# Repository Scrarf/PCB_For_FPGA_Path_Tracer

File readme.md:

# Work in progress!

PCB for [FPGA\_Path\_tracer](https://github.com/Scrarf/FPGA_Path_Tracer).

# Schematic

# Layout (WIP)

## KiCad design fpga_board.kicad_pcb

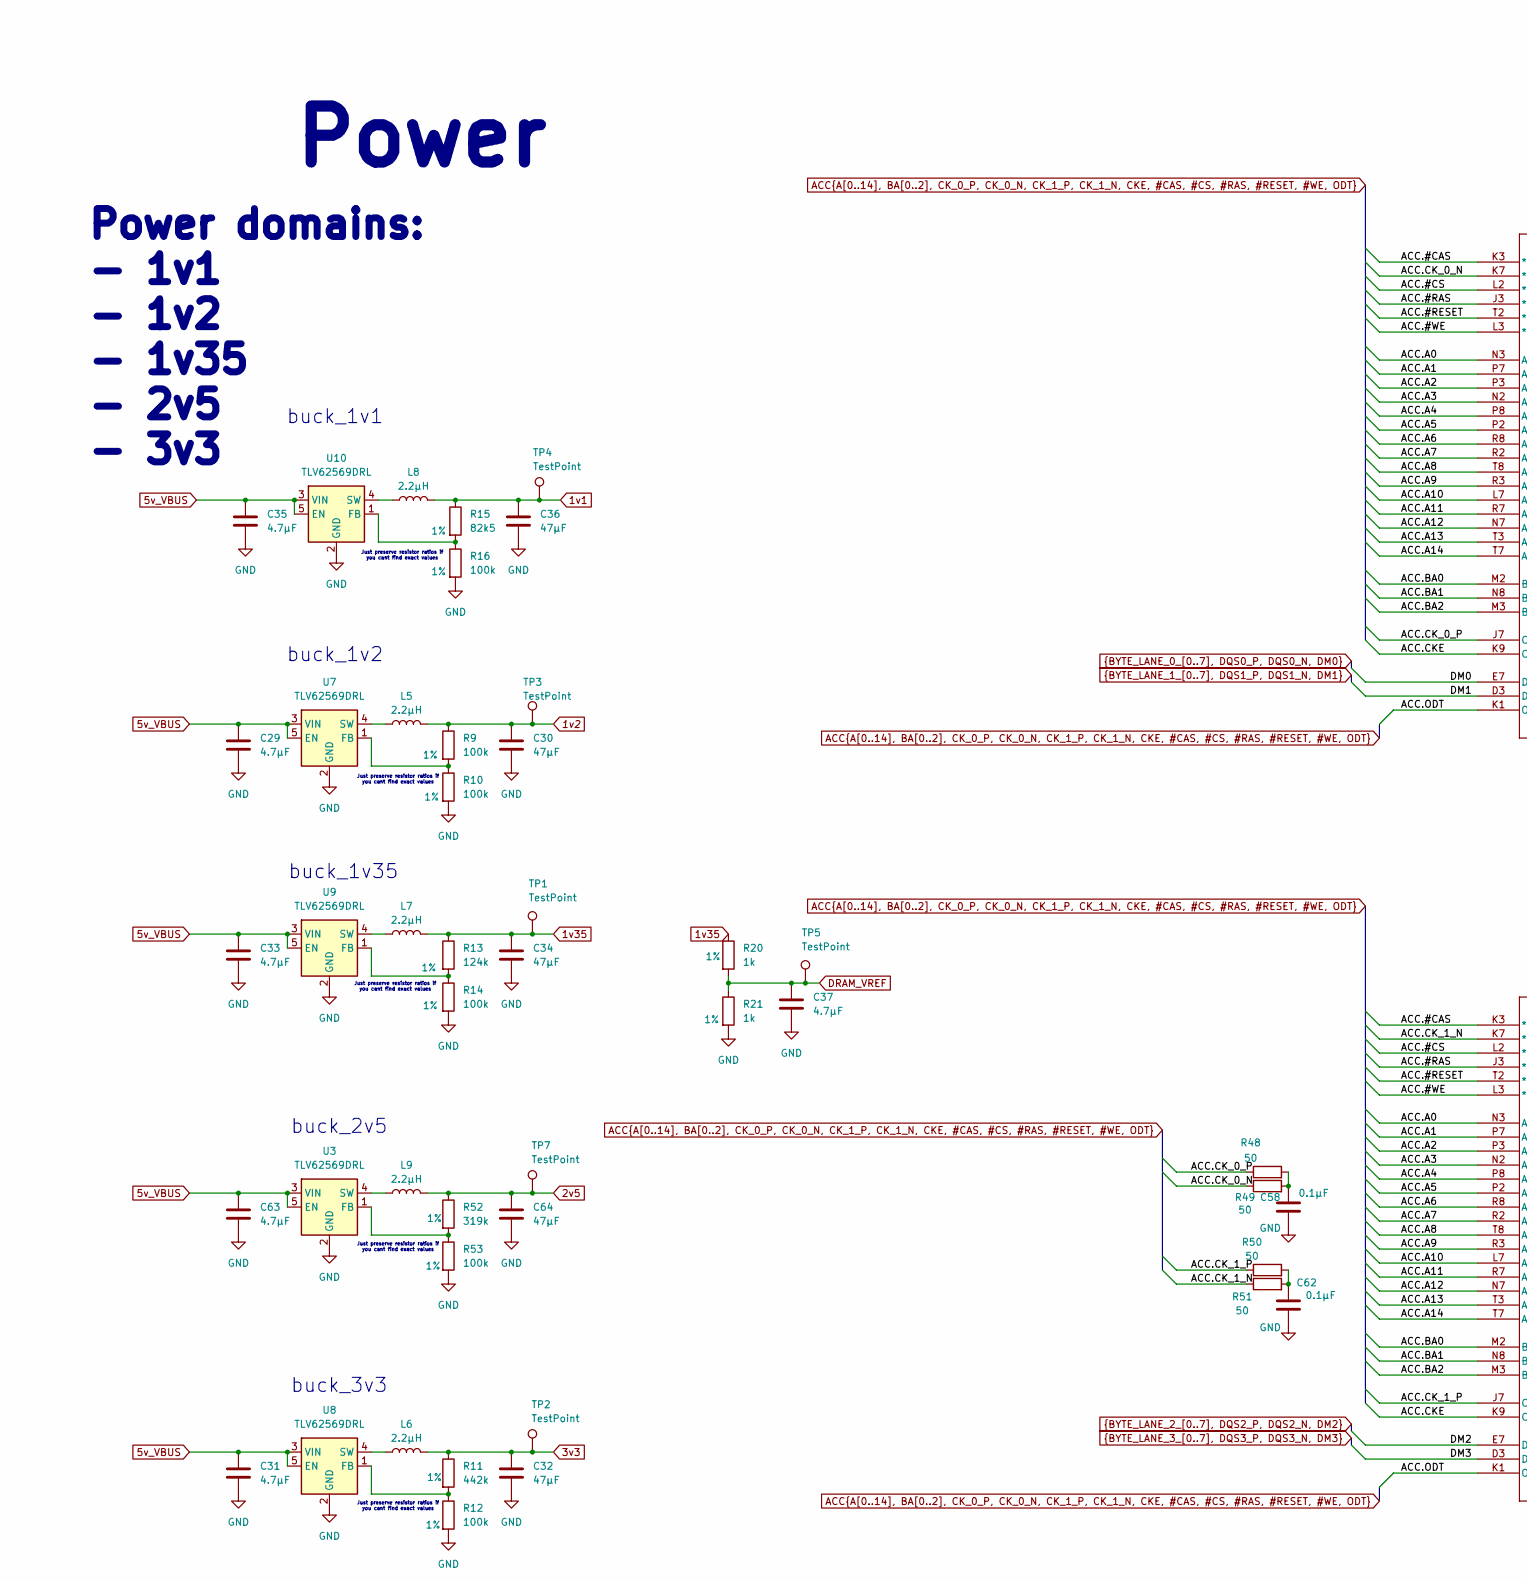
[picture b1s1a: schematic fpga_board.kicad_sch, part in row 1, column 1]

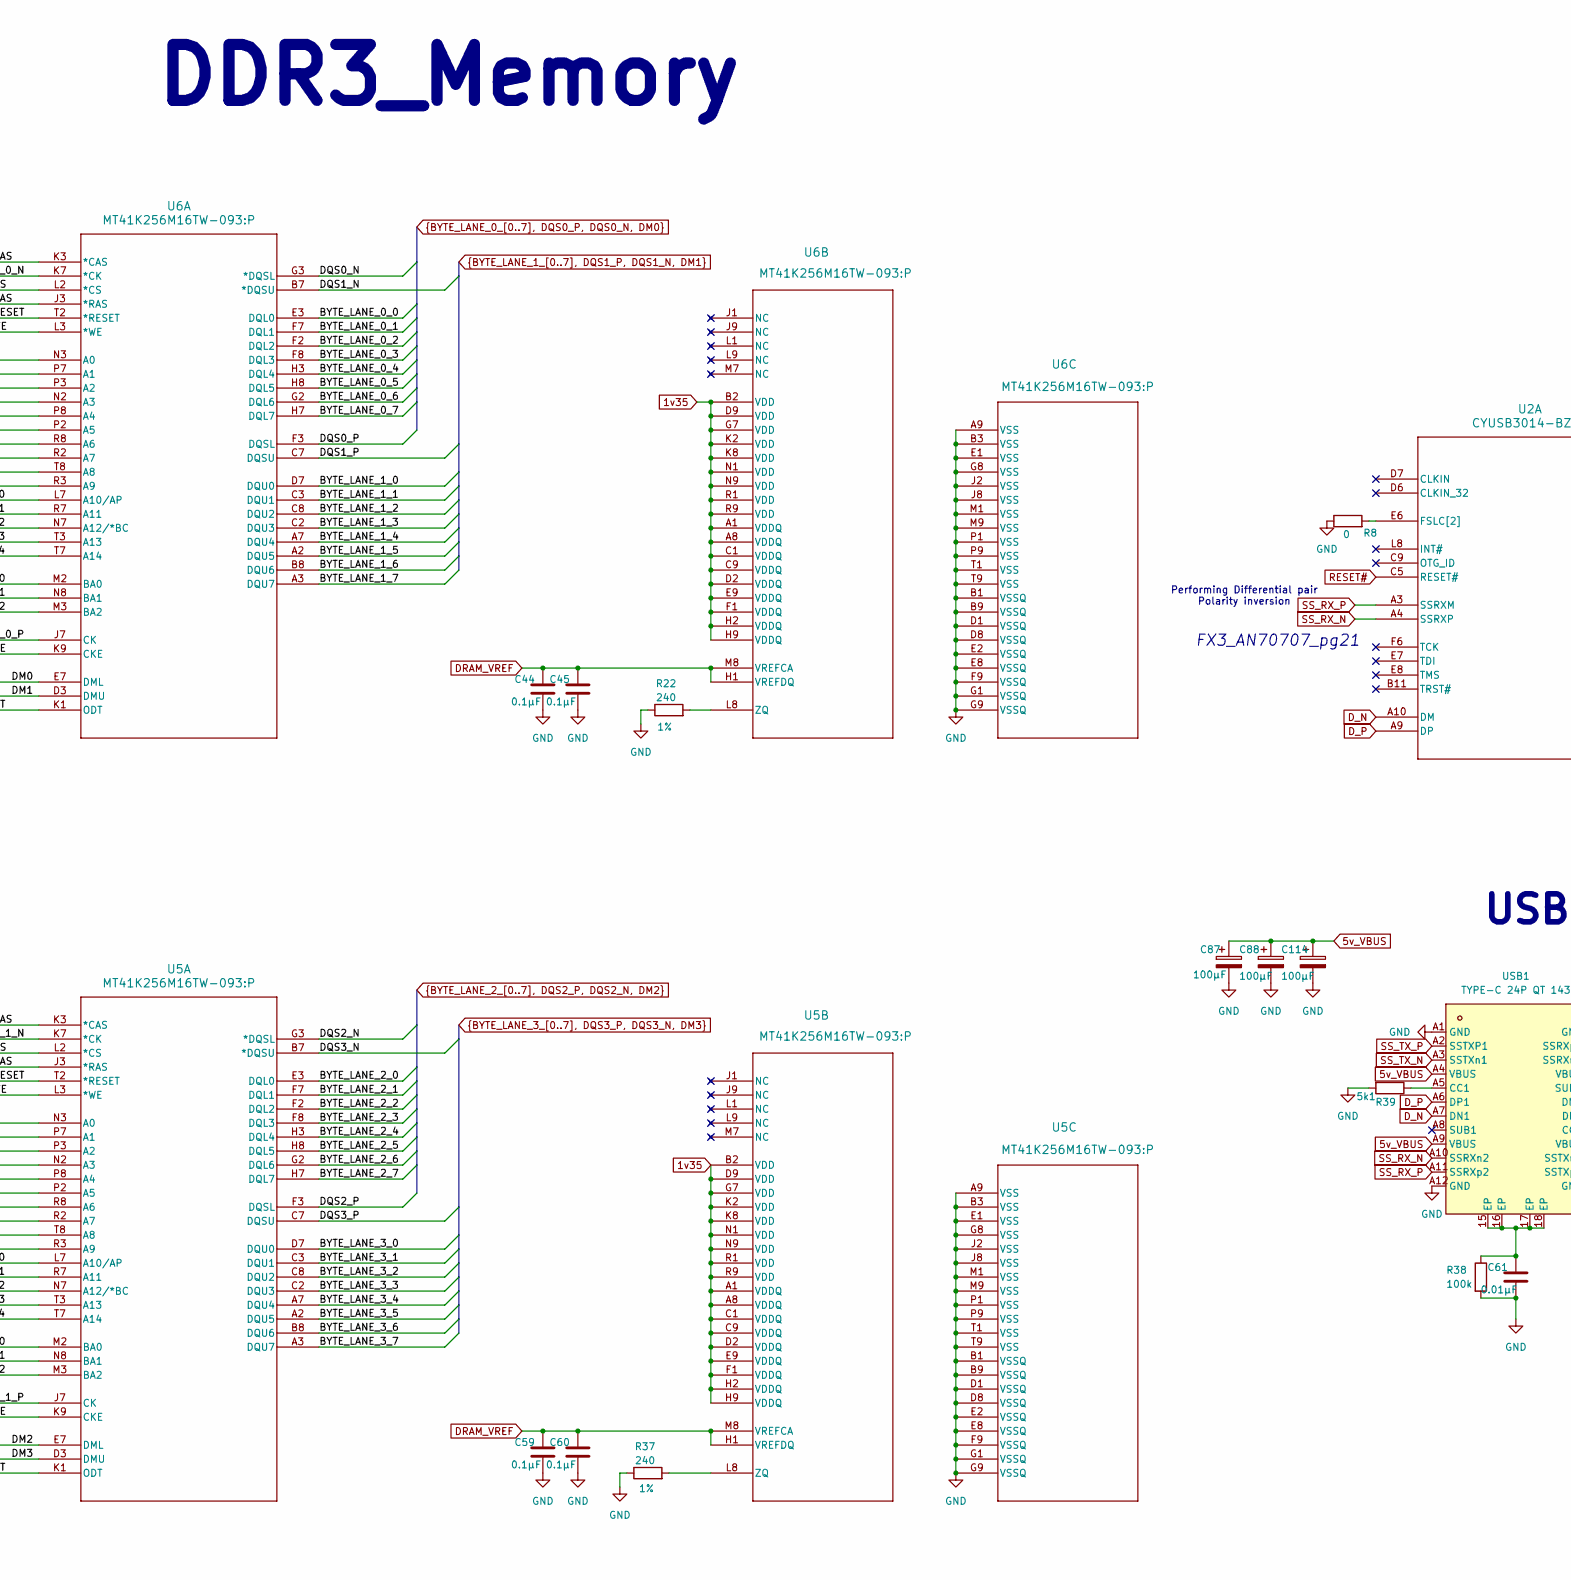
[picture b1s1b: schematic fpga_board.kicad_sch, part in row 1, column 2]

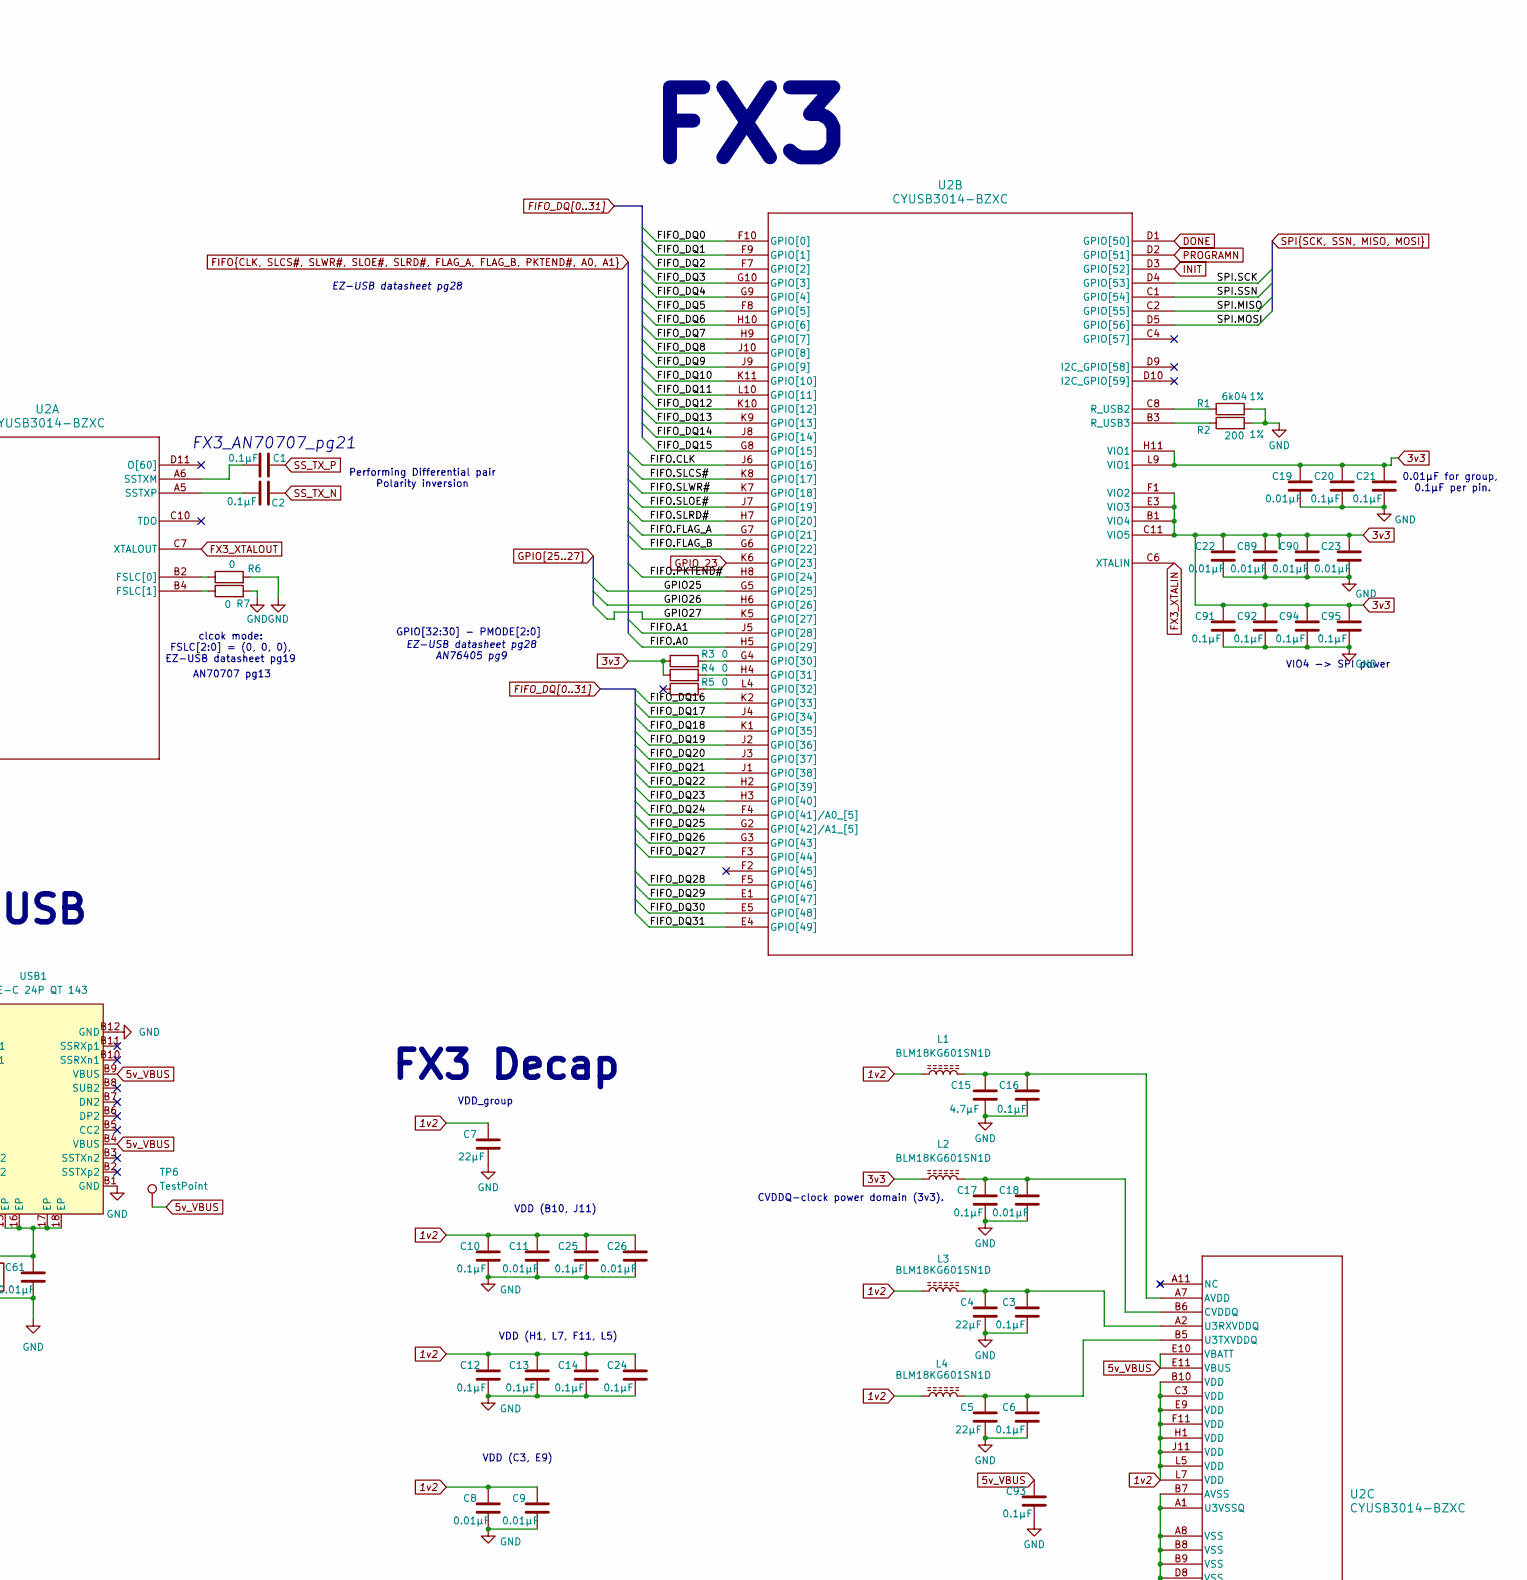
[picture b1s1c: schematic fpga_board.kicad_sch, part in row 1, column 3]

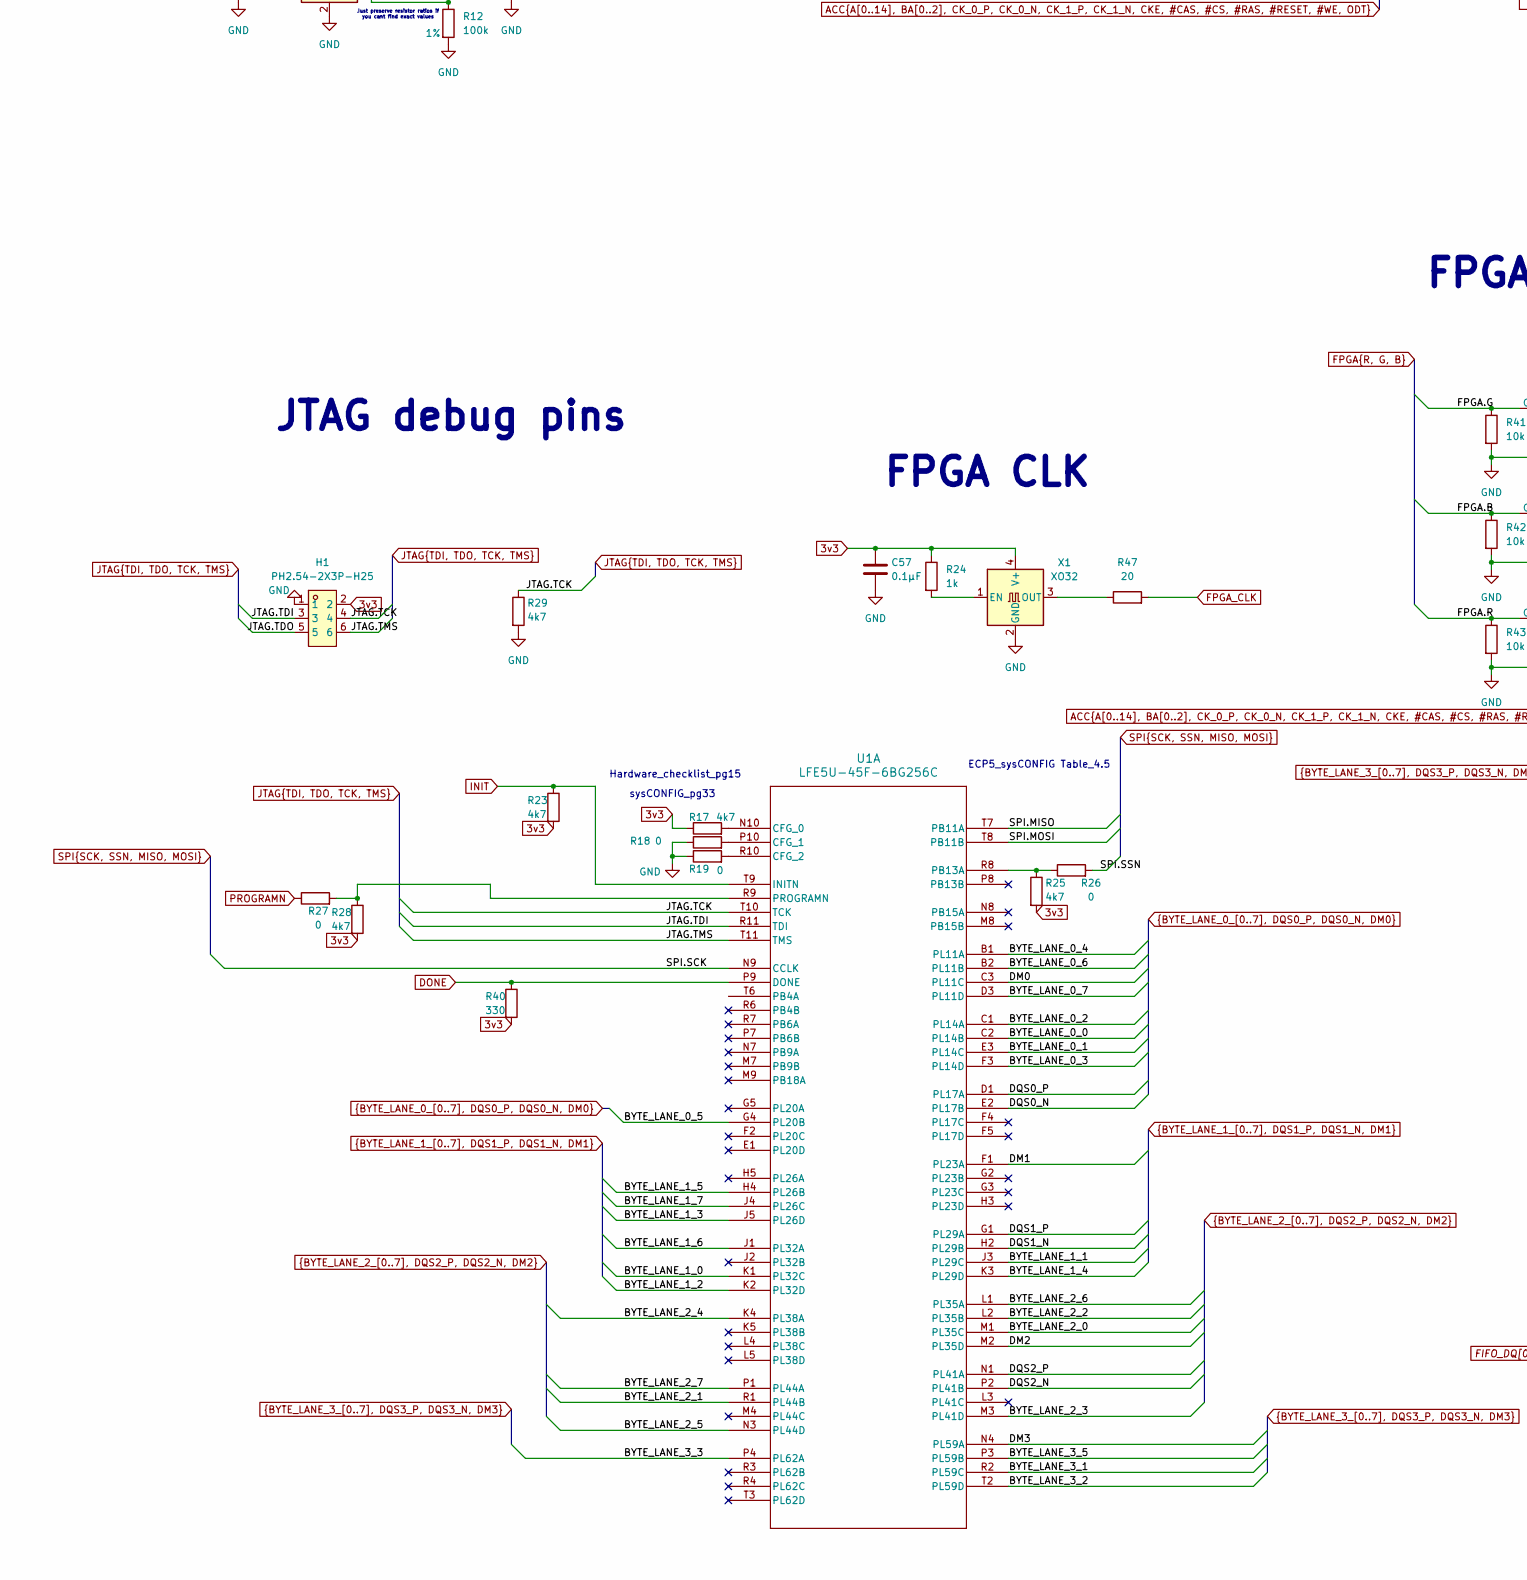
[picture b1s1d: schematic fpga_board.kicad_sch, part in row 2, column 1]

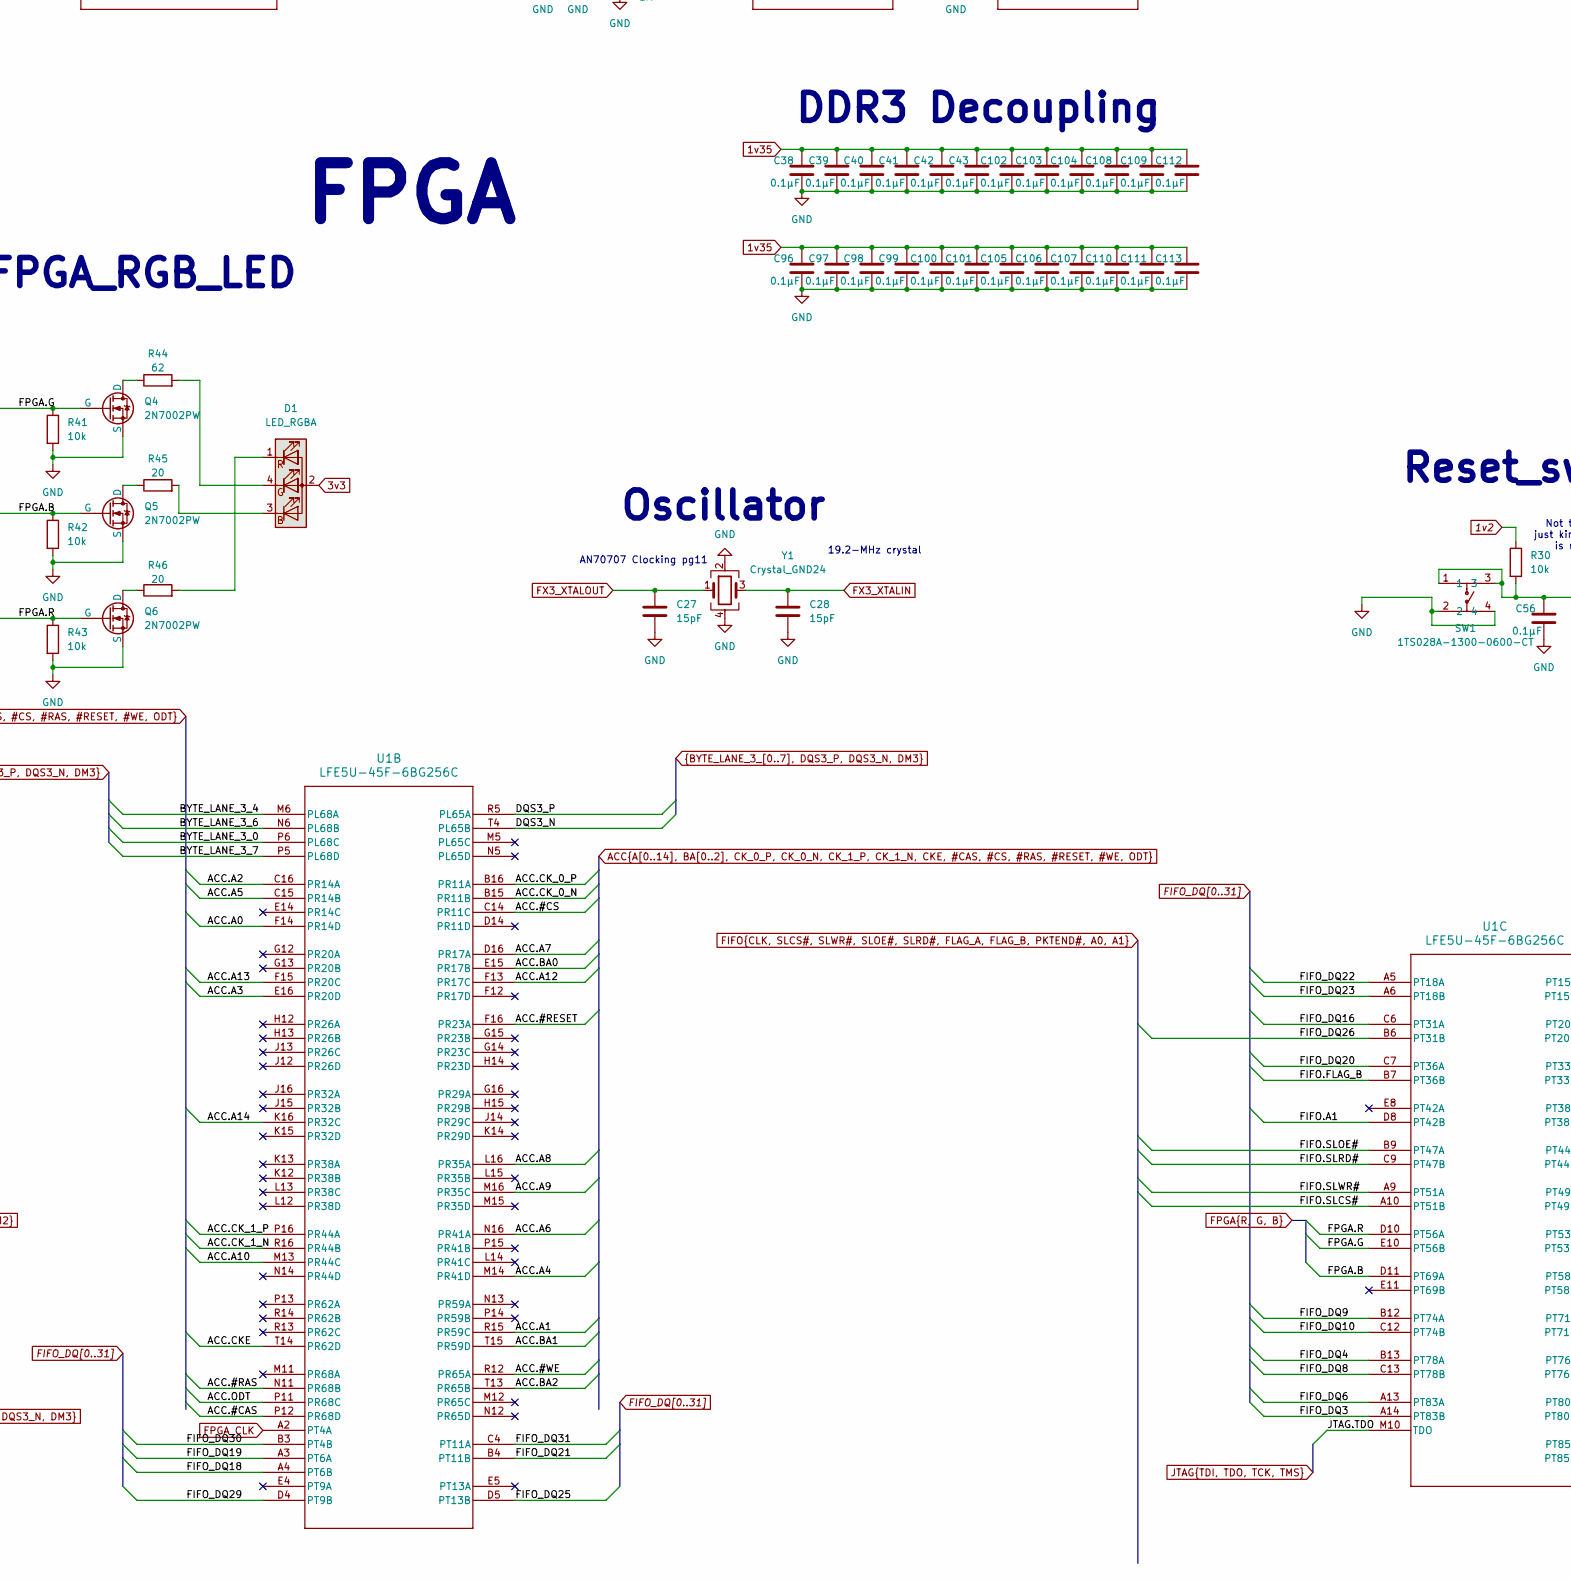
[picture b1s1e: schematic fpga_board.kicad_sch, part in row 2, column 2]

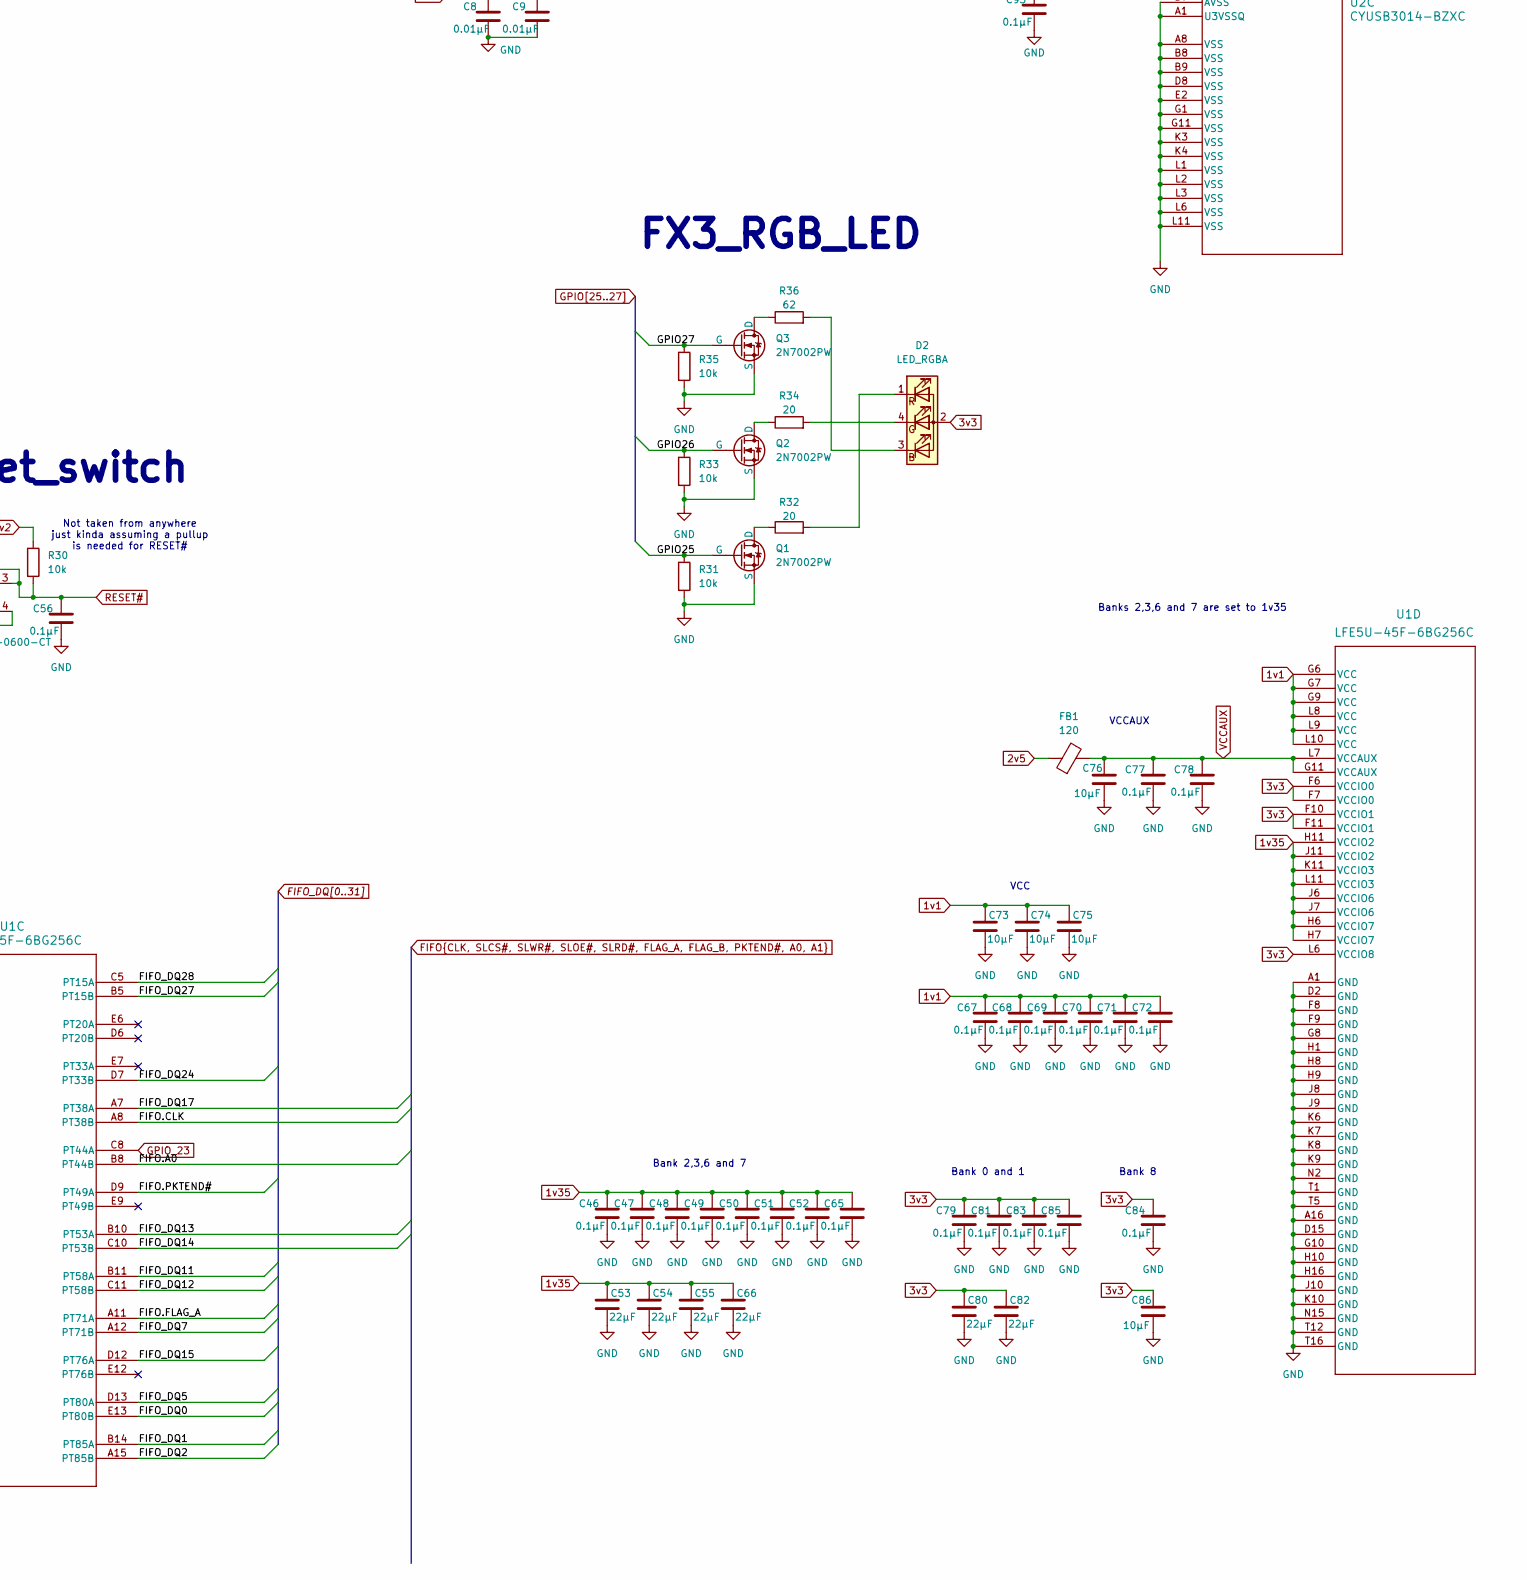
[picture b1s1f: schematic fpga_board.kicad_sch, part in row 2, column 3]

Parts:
C1, C2, C3, C6, C10, C12, C13, C14, C16, C17, C20, C21, C24, C25, C38, C39, C40, C41, C42, C43, C44, C45, C46, C47, C48, C49, C50, C51, C52, C56, C57, C58, C59, C60, C62, C65, C67, C68, C69, C70, C71, C72, C77, C78, C79, C81, C83, C84, C85, C91, C92, C93, C94, C95, C96, C97, C98, C99, C100, C101, C102, C103, C104, C105, C106, C107, C108, C109, C110, C111, C112, C113: 0.1µF; C_0402_1005Metric; LCSC Part C60474
C4, C5, C7, C53, C54, C55, C66, C80, C82: 22µF; C_0603_1608Metric; LCSC Part C6119868
C8, C9, C11, C18, C19, C22, C23, C26, C61, C89, C90: 0.01µF; C_0402_1005Metric; LCSC Part C22435944
C15, C29, C31, C33, C35, C37, C63: 4.7µF; C_0402_1005Metric; LCSC Part C6119786
C27, C28: 15pF; C_0402_1005Metric; LCSC Part C5448865
C30, C32, C34, C36, C64: 47µF; C_0805_2012Metric; LCSC Part C19103846
C73, C74, C75, C76, C86: 10µF; C_0402_1005Metric; LCSC Part C315248
C87, C88, C114: 100μF; CP_Elec_6.3x5.4; LCSC Part C2887276
D1, D2: LED_RGBA; LED_Wurth_150044M155260; LCSC Part C22461780
FB1: 120; L_0603_1608Metric; LCSC Part C307770
H1: PH2.54-2X3P-H25; HDR-TH_6P-P2.54-V-M-R2-C3-S2.54-1; LCSC Part C42431837
L1, L2, L3, L4: BLM18KG601SN1D; L_0603_1608Metric; LCSC Part C85833
L5, L6, L7, L8, L9: 2.2µH; IND_VLS3015_TDK; LCSC Part C42924311
Q1, Q2, Q3, Q4, Q5, Q6: 2N7002PW; SOT-323_SC-70; LCSC Part C7379955
R1: 6k04; R_0402_1005Metric; LCSC Part C168240
R2: 200; R_0402_1005Metric; LCSC Part C49655161
R3, R4, R5, R6, R7, R8, R18, R19, R26, R27: 0; R_0402_1005Metric; LCSC Part C106231
R9, R10, R12, R14, R16, R38, R53: 100k; R_0603_1608Metric; LCSC Part C14675
R11: 442k; R_0603_1608Metric; LCSC Part C3013201
R13: 124k; R_0603_1608Metric; LCSC Part C3016392
R15: 82k5; R_0603_1608Metric; LCSC Part C2999460
R17, R23, R25, R28, R29: 4k7; R_0402_1005Metric; LCSC Part C3017492
R20, R21, R24: 1k; R_0603_1608Metric; LCSC Part C22548
R22, R37: 240; R_0603_1608Metric; LCSC Part C49653074
R30, R31, R33, R35, R41, R42, R43: 10k; R_0402_1005Metric; LCSC Part C51035904
R32, R34, R45, R46, R47: 20; R_0402_1005Metric; LCSC Part C3017453
R36, R44: 62; R_0402_1005Metric; LCSC Part C49653021
R39: 5k1; R_0402_1005Metric; LCSC Part C49652827
R40: 330; R_0402_1005Metric; LCSC Part C2906929
R48, R49, R50, R51: 50; R_0402_1005Metric; LCSC Part C853312
R52: 319k; R_0603_1608Metric; LCSC Part C20165692
SW1: 1TS028A-1300-0600-CT; SW-SMD_4P-L2.8-W1.9-P1.20-LS3.0_1TS028A; LCSC Part C481983
TP1, TP2, TP3, TP4, TP5, TP6, TP7: TestPoint; TestPoint_Pad_D1.0mm
U1: LFE5U-45F-6BG256C; caBGA256_LAT; LCSC Part C1550834
U2: CYUSB3014-BZXC; TFBGA-121_10x10mm_Layout11x11_P0.8mm; LCSC Part C462526
U3, U7, U8, U9, U10: TLV62569DRL; SOT-563; LCSC Part C163217
U5, U6: MT41K256M16TW-093:P; Micron_FBGA-96_9x14mm_Layout9x16_P0.8mm; LCSC Part C2064402
USB1: TYPE-C 24P QT 143; TYPE-C-SMD_C9900025773; LCSC Part C5156605
X1: XO32; Crystal_SMD_5032-4Pin_5.0x3.2mm; LCSC Part C50345411
Y1: Crystal_GND24; Crystal_SMD_2520-4Pin_2.5x2.0mm; LCSC Part C7206296

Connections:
1v1: C36.1, C67.2, C68.2, C69.2, C70.2, C71.2, C72.2, C73.1, C74.1, C75.1, L8.2, R15.1, TP4.1, U1.G6 (VCC), U1.G7 (VCC), U1.G9 (VCC), U1.L8 (VCC), U1.L9 (VCC), U1.L10 (VCC)
1v2: C7.2, C8.2, C9.2, C10.2, C11.2, C12.2, C13.2, C14.2, C24.2, C25.2, C26.2, C30.1, L1.1, L3.1, L4.1, L5.2, R9.1, R30.1, TP3.1, U2.B10 (VDD), U2.C3 (VDD), U2.E9 (VDD), U2.F11 (VDD), U2.H1 (VDD), U2.J11 (VDD), U2.L5 (VDD), U2.L7 (VDD)
1v35: C34.1, C38.2, C39.2, C40.2, C41.2, C42.2, C43.2, C46.2, C47.2, C48.2, C49.2, C50.2, C51.2, C52.2, C53.1, C54.1, C55.1, C65.2, C66.1, C96.2, C97.2, C98.2, C99.2, C100.2, C101.2, C102.2, C103.2, C104.2, C105.2, C106.2, C107.2, C108.2, C109.2, C110.2, C111.2, C112.2, C113.2, L7.2, R13.1, R20.1, TP1.1, U1.H6 (VCCIO7), U1.H7 (VCCIO7), U1.H11 (VCCIO2), U1.J6 (VCCIO6), U1.J7 (VCCIO6), U1.J11 (VCCIO2), U1.K11 (VCCIO3), U1.L11 (VCCIO3), U5.A1 (VDDQ), U5.A8 (VDDQ), U5.B2 (VDD), U5.C1 (VDDQ), U5.C9 (VDDQ), U5.D2 (VDDQ), U5.D9 (VDD), U5.E9 (VDDQ), U5.F1 (VDDQ), U5.G7 (VDD), U5.H2 (VDDQ), U5.H9 (VDDQ), U5.K2 (VDD), U5.K8 (VDD), U5.N1 (VDD), U5.N9 (VDD), U5.R1 (VDD), U5.R9 (VDD), U6.A1 (VDDQ), U6.A8 (VDDQ), U6.B2 (VDD), U6.C1 (VDDQ), U6.C9 (VDDQ), U6.D2 (VDDQ), U6.D9 (VDD), U6.E9 (VDDQ), U6.F1 (VDDQ), U6.G7 (VDD), U6.H2 (VDDQ), U6.H9 (VDDQ), U6.K2 (VDD), U6.K8 (VDD), U6.N1 (VDD), U6.N9 (VDD), U6.R1 (VDD), U6.R9 (VDD)
2v5: C64.1, FB1.1, L9.2, R52.1, TP7.1
3v3: C19.2, C20.2, C21.2, C22.2, C23.2, C32.1, C57.1, C79.2, C80.1, C81.2, C82.1, C83.2, C84.2, C85.2, C86.1, C89.2, C90.2, C91.2, C92.2, C94.2, C95.2, D1.2 (A), D2.2 (A), H1.2, L2.1, L6.2, R3.1, R4.1, R11.1, R17.1, R23.2, R24.1, R25.2, R28.2, R40.2, TP2.1, U1.F6 (VCCIO0), U1.F7 (VCCIO0), U1.F10 (VCCIO1), U1.F11 (VCCIO1), U1.L6 (VCCIO8), U2.B1 (VIO4), U2.C11 (VIO5), U2.E3 (VIO3), U2.F1 (VIO2), U2.H11 (VIO1), U2.L9 (VIO1), X1.4 (V+)
5v_VBUS: C29.1, C31.1, C33.1, C35.1, C63.1, C87.1, C88.1, C93.2, C114.1, TP6.1, U2.E10 (VBATT), U2.E11 (VBUS), U3.3 (VIN), U3.5 (EN), U7.3 (VIN), U7.5 (EN), U8.3 (VIN), U8.5 (EN), U9.3 (VIN), U9.5 (EN), U10.3 (VIN), U10.5 (EN), USB1.A4 (VBUS), USB1.A9 (VBUS), USB1.B4 (VBUS), USB1.B9 (VBUS)
ACC.#CAS: U1.P12 (PR68D), U5.K3 (*CAS), U6.K3 (*CAS)
ACC.#CS: U1.C14 (PR11C), U5.L2 (*CS), U6.L2 (*CS)
ACC.#RAS: U1.N11 (PR68B), U5.J3 (*RAS), U6.J3 (*RAS)
ACC.#RESET: U1.F16 (PR23A), U5.T2 (*RESET), U6.T2 (*RESET)
ACC.#WE: U1.R12 (PR65A), U5.L3 (*WE), U6.L3 (*WE)
ACC.A0: U1.F14 (PR14D), U5.N3 (A0), U6.N3 (A0)
ACC.A1: U1.R15 (PR59C), U5.P7 (A1), U6.P7 (A1)
ACC.A2: U1.C16 (PR14A), U5.P3 (A2), U6.P3 (A2)
ACC.A3: U1.E16 (PR20D), U5.N2 (A3), U6.N2 (A3)
ACC.A4: U1.M14 (PR41D), U5.P8 (A4), U6.P8 (A4)
ACC.A5: U1.C15 (PR14B), U5.P2 (A5), U6.P2 (A5)
ACC.A6: U1.N16 (PR41A), U5.R8 (A6), U6.R8 (A6)
ACC.A7: U1.D16 (PR17A), U5.R2 (A7), U6.R2 (A7)
ACC.A8: U1.L16 (PR35A), U5.T8 (A8), U6.T8 (A8)
ACC.A9: U1.M16 (PR35C), U5.R3 (A9), U6.R3 (A9)
ACC.A10: U1.M13 (PR44C), U5.L7 (A10/AP), U6.L7 (A10/AP)
ACC.A11: U5.R7 (A11), U6.R7 (A11)
ACC.A12: U1.F13 (PR17C), U5.N7 (A12/*BC), U6.N7 (A12/*BC)
ACC.A13: U1.F15 (PR20C), U5.T3 (A13), U6.T3 (A13)
ACC.A14: U1.K16 (PR32C), U5.T7 (A14), U6.T7 (A14)
ACC.BA0: U1.E15 (PR17B), U5.M2 (BA0), U6.M2 (BA0)
ACC.BA1: U1.T15 (PR59D), U5.N8 (BA1), U6.N8 (BA1)
ACC.BA2: U1.T13 (PR65B), U5.M3 (BA2), U6.M3 (BA2)
ACC.CKE: U1.T14 (PR62D), U5.K9 (CKE), U6.K9 (CKE)
ACC.CK_0_N: R49.1, U1.B15 (PR11B), U6.K7 (*CK)
ACC.CK_0_P: R48.1, U1.B16 (PR11A), U6.J7 (CK)
ACC.CK_1_N: R51.1, U1.R16 (PR44B), U5.K7 (*CK)
ACC.CK_1_P: R50.1, U1.P16 (PR44A), U5.J7 (CK)
ACC.ODT: U1.P11 (PR68C), U5.K1 (ODT), U6.K1 (ODT)
BYTE_LANE_0_0: U1.C2 (PL14B), U6.E3 (DQL0)
BYTE_LANE_0_1: U1.E3 (PL14C), U6.F7 (DQL1)
BYTE_LANE_0_2: U1.C1 (PL14A), U6.F2 (DQL2)
BYTE_LANE_0_3: U1.F3 (PL14D), U6.F8 (DQL3)
BYTE_LANE_0_4: U1.B1 (PL11A), U6.H3 (DQL4)
BYTE_LANE_0_5: U1.G4 (PL20B), U6.H8 (DQL5)
BYTE_LANE_0_6: U1.B2 (PL11B), U6.G2 (DQL6)
BYTE_LANE_0_7: U1.D3 (PL11D), U6.H7 (DQL7)
BYTE_LANE_1_0: U1.K1 (PL32C), U6.D7 (DQU0)
BYTE_LANE_1_1: U1.J3 (PL29C), U6.C3 (DQU1)
BYTE_LANE_1_2: U1.K2 (PL32D), U6.C8 (DQU2)
BYTE_LANE_1_3: U1.J5 (PL26D), U6.C2 (DQU3)
BYTE_LANE_1_4: U1.K3 (PL29D), U6.A7 (DQU4)
BYTE_LANE_1_5: U1.H4 (PL26B), U6.A2 (DQU5)
BYTE_LANE_1_6: U1.J1 (PL32A), U6.B8 (DQU6)
BYTE_LANE_1_7: U1.J4 (PL26C), U6.A3 (DQU7)
BYTE_LANE_2_0: U1.M1 (PL35C), U5.E3 (DQL0)
BYTE_LANE_2_1: U1.R1 (PL44B), U5.F7 (DQL1)
BYTE_LANE_2_2: U1.L2 (PL35B), U5.F2 (DQL2)
BYTE_LANE_2_3: U1.M3 (PL41D), U5.F8 (DQL3)
BYTE_LANE_2_4: U1.K4 (PL38A), U5.H3 (DQL4)
BYTE_LANE_2_5: U1.N3 (PL44D), U5.H8 (DQL5)
BYTE_LANE_2_6: U1.L1 (PL35A), U5.G2 (DQL6)
BYTE_LANE_2_7: U1.P1 (PL44A), U5.H7 (DQL7)
BYTE_LANE_3_0: U1.P6 (PL68C), U5.D7 (DQU0)
BYTE_LANE_3_1: U1.R2 (PL59C), U5.C3 (DQU1)
BYTE_LANE_3_2: U1.T2 (PL59D), U5.C8 (DQU2)
BYTE_LANE_3_3: U1.P4 (PL62A), U5.C2 (DQU3)
BYTE_LANE_3_4: U1.M6 (PL68A), U5.A7 (DQU4)
BYTE_LANE_3_5: U1.P3 (PL59B), U5.A2 (DQU5)
BYTE_LANE_3_6: U1.N6 (PL68B), U5.B8 (DQU6)
BYTE_LANE_3_7: U1.P5 (PL68D), U5.A3 (DQU7)
DM0: U1.C3 (PL11C), U6.E7 (DML)
DM1: U1.F1 (PL23A), U6.D3 (DMU)
DM2: U1.M2 (PL35D), U5.E7 (DML)
DM3: U1.N4 (PL59A), U5.D3 (DMU)
DONE: R40.1, U1.P9 (DONE), U2.D1 (GPIO[50])
DQS0_N: U1.E2 (PL17B), U6.G3 (*DQSL)
DQS0_P: U1.D1 (PL17A), U6.F3 (DQSL)
DQS1_N: U1.H2 (PL29B), U6.B7 (*DQSU)
DQS1_P: U1.G1 (PL29A), U6.C7 (DQSU)
DQS2_N: U1.P2 (PL41B), U5.G3 (*DQSL)
DQS2_P: U1.N1 (PL41A), U5.F3 (DQSL)
DQS3_N: U1.T4 (PL65B), U5.B7 (*DQSU)
DQS3_P: U1.R5 (PL65A), U5.C7 (DQSU)
DRAM_VREF: C37.1, C44.2, C45.2, C59.2, C60.2, R20.2, R21.1, TP5.1, U5.H1 (VREFDQ), U5.M8 (VREFCA), U6.H1 (VREFDQ), U6.M8 (VREFCA)
D_N: U2.A10 (DM), USB1.A7 (DN1)
D_P: U2.A9 (DP), USB1.A6 (DP1)
FIFO.A0: U1.B8 (PT44B), U2.H5 (GPIO[29])
FIFO.A1: U1.D8 (PT42B), U2.J5 (GPIO[28])
FIFO.CLK: U1.A8 (PT38B), U2.J6 (GPIO[16])
FIFO.FLAG_A: U1.A11 (PT71A), U2.G7 (GPIO[21])
FIFO.FLAG_B: U1.B7 (PT36B), U2.G6 (GPIO[22])
FIFO.PKTEND#: U1.D9 (PT49A), U2.H8 (GPIO[24])
FIFO.SLCS#: U1.A10 (PT51B), U2.K8 (GPIO[17])
FIFO.SLOE#: U1.B9 (PT47A), U2.J7 (GPIO[19])
FIFO.SLRD#: U1.C9 (PT47B), U2.H7 (GPIO[20])
FIFO.SLWR#: U1.A9 (PT51A), U2.K7 (GPIO[18])
FIFO_DQ0: U1.E13 (PT80B), U2.F10 (GPIO[0])
FIFO_DQ1: U1.B14 (PT85A), U2.F9 (GPIO[1])
FIFO_DQ2: U1.A15 (PT85B), U2.F7 (GPIO[2])
FIFO_DQ3: U1.A14 (PT83B), U2.G10 (GPIO[3])
FIFO_DQ4: U1.B13 (PT78A), U2.G9 (GPIO[4])
FIFO_DQ5: U1.D13 (PT80A), U2.F8 (GPIO[5])
FIFO_DQ6: U1.A13 (PT83A), U2.H10 (GPIO[6])
FIFO_DQ7: U1.A12 (PT71B), U2.H9 (GPIO[7])
FIFO_DQ8: U1.C13 (PT78B), U2.J10 (GPIO[8])
FIFO_DQ9: U1.B12 (PT74A), U2.J9 (GPIO[9])
FIFO_DQ10: U1.C12 (PT74B), U2.K11 (GPIO[10])
FIFO_DQ11: U1.B11 (PT58A), U2.L10 (GPIO[11])
FIFO_DQ12: U1.C11 (PT58B), U2.K10 (GPIO[12])
FIFO_DQ13: U1.B10 (PT53A), U2.K9 (GPIO[13])
FIFO_DQ14: U1.C10 (PT53B), U2.J8 (GPIO[14])
FIFO_DQ15: U1.D12 (PT76A), U2.G8 (GPIO[15])
FIFO_DQ16: U1.C6 (PT31A), U2.K2 (GPIO[33])
FIFO_DQ17: U1.A7 (PT38A), U2.J4 (GPIO[34])
FIFO_DQ18: U1.A4 (PT6B), U2.K1 (GPIO[35])
FIFO_DQ19: U1.A3 (PT6A), U2.J2 (GPIO[36])
FIFO_DQ20: U1.C7 (PT36A), U2.J3 (GPIO[37])
FIFO_DQ21: U1.B4 (PT11B), U2.J1 (GPIO[38])
FIFO_DQ22: U1.A5 (PT18A), U2.H2 (GPIO[39])
FIFO_DQ23: U1.A6 (PT18B), U2.H3 (GPIO[40])
FIFO_DQ24: U1.D7 (PT33B), U2.F4 (GPIO[41]/A0_[5])
FIFO_DQ25: U1.D5 (PT13B), U2.G2 (GPIO[42]/A1_[5])
FIFO_DQ26: U1.B6 (PT31B), U2.G3 (GPIO[43])
FIFO_DQ27: U1.B5 (PT15B), U2.F3 (GPIO[44])
FIFO_DQ28: U1.C5 (PT15A), U2.F5 (GPIO[46])
FIFO_DQ29: U1.D4 (PT9B), U2.E1 (GPIO[47])
FIFO_DQ30: U1.B3 (PT4B), U2.E5 (GPIO[48])
FIFO_DQ31: U1.C4 (PT11A), U2.E4 (GPIO[49])
FPGA.B: Q5.2 (G), R42.1, U1.D11 (PT69A)
FPGA.G: Q4.2 (G), R41.1, U1.E10 (PT56B)
FPGA.R: Q6.2 (G), R43.1, U1.D10 (PT56A)
FPGA_CLK: R47.2, U1.A2 (PT4A)
FX3_XTALIN: C28.1, U2.C6 (XTALIN), Y1.3
FX3_XTALOUT: C27.1, U2.C7 (XTALOUT), Y1.1
GND: C3.1, C4.1, C5.1, C6.1, C7.1, C8.1, C9.1, C10.1, C11.1, C12.1, C13.1, C14.1, C15.2, C16.1, C17.1, C18.1, C19.1, C20.1, C21.1, C22.1, C23.1, C24.1, C25.1, C26.1, C27.2, C28.2, C29.2, C30.2, C31.2, C32.2, C33.2, C34.2, C35.2, C36.2, C37.2, C38.1, C39.1, C40.1, C41.1, C42.1, C43.1, C44.1, C45.1, C46.1, C47.1, C48.1, C49.1, C50.1, C51.1, C52.1, C53.2, C54.2, C55.2, C56.1, C57.2, C58.1, C59.1, C60.1, C61.1, C62.1, C63.2, C64.2, C65.1, C66.2, C67.1, C68.1, C69.1, C70.1, C71.1, C72.1, C73.2, C74.2, C75.2, C76.2, C77.1, C78.1, C79.1, C80.2, C81.1, C82.2, C83.1, C84.1, C85.1, C86.2, C87.2, C88.2, C89.1, C90.1, C91.1, C92.1, C93.1, C94.1, C95.1, C96.1, C97.1, C98.1, C99.1, C100.1, C101.1, C102.1, C103.1, C104.1, C105.1, C106.1, C107.1, C108.1, C109.1, C110.1, C111.1, C112.1, C113.1, C114.2, H1.1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
GPIO25: Q1.2 (G), R31.1, U2.G5 (GPIO[25])
GPIO26: Q2.2 (G), R33.1, U2.H6 (GPIO[26])
GPIO27: Q3.2 (G), R35.1, U2.K5 (GPIO[27])
GPIO_23: U1.C8 (PT44A), U2.K6 (GPIO[23])
INIT: R23.1, U1.T9 (INITN), U2.D3 (GPIO[52])
JTAG.TCK: H1.4, R29.1, U1.T10 (TCK)
JTAG.TDI: H1.3, U1.R11 (TDI)
JTAG.TDO: H1.5, U1.M10 (TDO)
JTAG.TMS: H1.6, U1.T11 (TMS)
unnamed: C58.2, R48.2, R49.2
unnamed: C61.2, R38.1, USB1.15 (EP), USB1.16 (EP), USB1.17 (EP), USB1.18 (EP)
unnamed: C62.2, R50.2, R51.2
unnamed: D1.3 (BK), R45.2
unnamed: D1.4 (GK), R44.2
unnamed: D1.1 (RK), R46.2
unnamed: D2.3 (BK), R36.2
unnamed: D2.4 (GK), R34.2
unnamed: D2.1 (RK), R32.2
unnamed: Q1.1 (D), R32.1
unnamed: Q2.1 (D), R34.1
unnamed: Q3.1 (D), R36.1
unnamed: Q4.1 (D), R44.1
unnamed: Q5.1 (D), R45.1
unnamed: Q6.1 (D), R46.1
unnamed: R17.2, U1.N10 (CFG_0)
unnamed: R18.2, U1.P10 (CFG_1)
unnamed: R19.2, U1.R10 (CFG_2)
unnamed: R25.1, R26.1, U1.R8 (PB13A)
unnamed: R27.2, R28.1, U1.R9 (PROGRAMN)
unnamed: R6.1, U2.B2 (FSLC[0])
unnamed: R7.1, U2.B4 (FSLC[1])
unnamed: R8.2, U2.E6 (FSLC[2])
unnamed: C1.1, U2.A6 (SSTXM)
unnamed: C2.1, U2.A5 (SSTXP)
unnamed: R3.2, U2.G4 (GPIO[30])
unnamed: R4.2, U2.H4 (GPIO[31])
unnamed: R5.2, U2.L4 (GPIO[32])
unnamed: R1.1, U2.C8 (R_USB2)
unnamed: R2.1, U2.B3 (R_USB3)
unnamed: C15.1, C16.2, L1.2, U2.A7 (AVDD)
unnamed: C17.2, C18.2, L2.2, U2.B6 (CVDDQ)
unnamed: C3.2, C4.2, L3.2, U2.A2 (U3RXVDDQ)
unnamed: C5.2, C6.2, L4.2, U2.B5 (U3TXVDDQ)
unnamed: R52.2, R53.1, U3.1 (FB)
unnamed: L9.1, U3.4 (SW)
unnamed: R37.2, U5.L8 (ZQ)
unnamed: R22.2, U6.L8 (ZQ)
unnamed: R9.2, R10.1, U7.1 (FB)
unnamed: L5.1, U7.4 (SW)
unnamed: R11.2, R12.1, U8.1 (FB)
unnamed: L6.1, U8.4 (SW)
unnamed: R13.2, R14.1, U9.1 (FB)
unnamed: L7.1, U9.4 (SW)
unnamed: R15.2, R16.1, U10.1 (FB)
unnamed: L8.1, U10.4 (SW)
unnamed: R39.1, USB1.A5 (CC1)
unnamed: R24.2, X1.1 (EN)
unnamed: R47.1, X1.3 (OUT)
PROGRAMN: R27.1, U2.D2 (GPIO[51])
RESET#: C56.2, R30.2, SW1.1, SW1.3, U2.C5 (RESET#)
SPI.MISO: U1.T7 (PB11A), U2.C2 (GPIO[55])
SPI.MOSI: U1.T8 (PB11B), U2.D5 (GPIO[56])
SPI.SCK: U1.N9 (CCLK), U2.D4 (GPIO[53])
SPI.SSN: R26.2, U2.C1 (GPIO[54])
SS_RX_N: U2.A4 (SSRXP), USB1.A10 (SSRXn2)
SS_RX_P: U2.A3 (SSRXM), USB1.A11 (SSRXp2)
SS_TX_N: C2.2, USB1.A3 (SSTXn1)
SS_TX_P: C1.2, USB1.A2 (SSTXP1)
VCCAUX: C76.1, C77.2, C78.2, FB1.2, U1.G11 (VCCAUX), U1.L7 (VCCAUX)

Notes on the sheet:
VDD (C3, E9)
GPIO[32:30] - PMODE[2:0]
Banks 2,3,6 and 7 are set to 1v35
Performing Differential pair Polarity inversion
Power
clcok mode: FSLC[2:0] = (0, 0, 0), EZ-USB datasheet pg19
Just preserve resistor ratios if you cant find exact values
VCCAUX
buck_1v35
buck_2v5
AN70707 pg13
VDD (B10, J11)
FPGA_RGB_LED
FX3
VCC
DDR3 Decoupling
VDD_group
buck_1v2
VDD (H1, L7, F11, L5)
19.2-MHz crystal
buck_1v1
FPGA CLK
buck_3v3
FX3 Decap
Not taken from anywhere just kinda assuming a pullup is needed for RESET#
Hardware_checklist_pg15
Bank 0 and 1
AN70707 Clocking pg11
0.01µF for group, 0.1µF per pin.
USB
EZ-USB datasheet pg28 AN76405 pg9
Bank 8
DDR3_Memory
sysCONFIG_pg33
Bank 2,3,6 and 7
Oscillator
ECP5_sysCONFIG Table_4.5
FX3_AN70707_pg21
FX3_RGB_LED
FPGA
